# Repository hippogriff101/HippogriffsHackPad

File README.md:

# HippogriffsHackPad
A project for Hack Club's [Blueprint](blueprint.hackclub.com), that ends in _less than_ 24 hours!

_Yes_, I made this in ONE day!

_Yes_, it is probebly not very good!

_Yes_, this is the first time using fusion and second time using KiCad!

### BOM 

_(KiCad made this idk what it means)_

| Reference | Value | Footprint | Datasheet | Qty | DNP | Exclude from BOM | Exclude from Board |
| :--- | :--- | :--- | :--- | :--- | :--- | :--- | :--- |
| SW1, SW2, SW3 | SW_Push | Button_Switch_Keyboard:SW_Cherry_MX_1.00u_PCB | ~ | 3 | | | |
| SW4 | RotaryEncoder_Switch | Rotary_Encoder:RotaryEncoder_Alps_EC11E-Switch_Vertical_H20mm | ~ | 1 | | | |
| U1 | MOUDLE-SEEEDUINO-XIAO | Footprints?:XIAO-Generic-Hybrid-14P-2.54-21X17.8MM | | 1 | | | |

### PCB

Here is some images of the schematic and PCB design I made in KiCad!

> Schematic Editor

> PCB Editor

> 3D Preview of PCB

### CAD

> [`Hippogriff's Hack Pad.stl`](https://github.com/hippogriff101/HippogriffsHackPad/blob/main/CAD/Hippogriff's%20Hack%20Pad.stl)

### Blueprint Requirments

#### What is my project, how will I use it adn why I made it?

This is a project that follows the [Blueprint Hackpad](https://blueprint.hackclub.com/hackpad/) Guided Project. However, to make it my own I added a Rotary Encoder that I can use to change volume or control lights in my room! The other butttons on my Hackpad could be used to activate certain functions etc. that make my life easier. Now, the reason for making this is, as you can see, I am in first 250 users to create an account and this project was created on Blueprint four months ago but I have only gotten around to making it in the last 10 hours of the event. WHile I'm not the best at hardware I have given it a go and hope to make something cool!

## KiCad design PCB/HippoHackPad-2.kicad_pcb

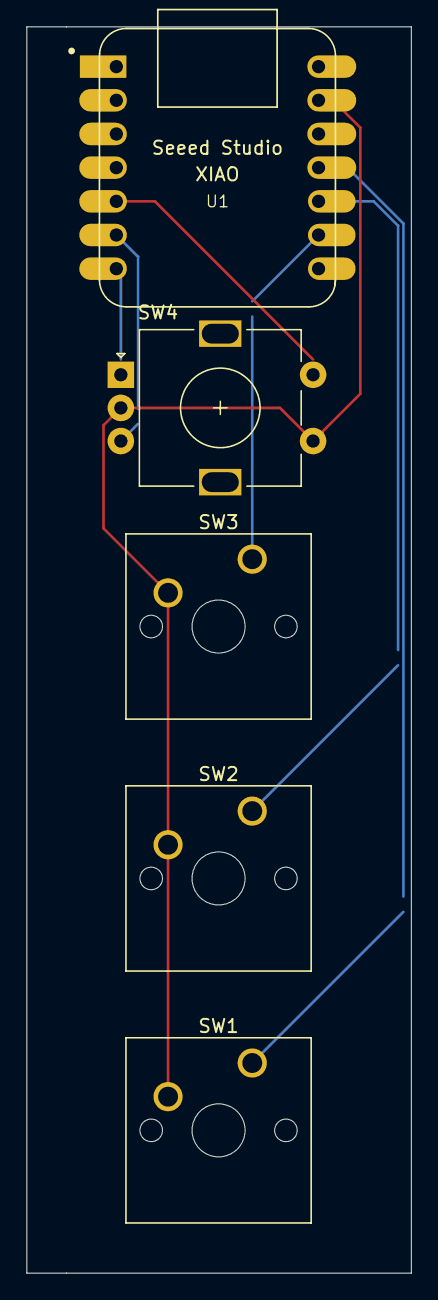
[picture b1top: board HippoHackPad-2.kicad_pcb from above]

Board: 2 copper layers, 29.0 x 94.0 mm, 5 parts (0 on the bottom side), 7 nets.

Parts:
SW1, SW2, SW3: SW_Push; SW_Cherry_MX_1.00u_PCB
SW4: RotaryEncoder_Switch; RotaryEncoder_Alps_EC11E-Switch_Vertical_H20mm
U1: MOUDLE-SEEEDUINO-XIAO; XIAO-Generic-Hybrid-14P-2.54-21X17.8MM

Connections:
GND: SW1.2, SW2.2, SW3.2, SW4.C, SW4.f (S1), U1.13 (GND)
unnamed: SW2.1, U1.10 (PA5_A9_D9_MISO)
unnamed: SW1.1, U1.11 (PA6_A10_D10_MOSI)
unnamed: SW3.1, U1.9 (PA7_A8_D8_SCK)
unnamed: SW4.S2, U1.5 (PA8_A4_D4_SDA)
unnamed: SW4.B, U1.6 (PA9_A5_D5_SCL)
unnamed: SW4.A, U1.7 (PB08_A6_D6_TX)

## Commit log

2026-03-31 PCB and Case design
2026-03-31 Refactor code structure for improved readability and maintainability
2026-03-31 Add MIT License to the project
2026-03-31 Update README with Blueprint Requirements section
    Added a section on Blueprint Requirements detailing the project purpose and features.
2026-03-31 Add Gerber files and CAD files
    - Added Gerber files for various layers including Copper, Mask, Paste, Silkscreen, and Edge Cuts.
    - Created a f3d and STEP file for CAD output
2026-03-31 Update PCB files and add BOM for components
2026-03-31 Update BOM with corrected unit prices and added keycaps
2026-03-31 Update .gitignore to include firmware directory
2026-03-31 Add seperated STEP files
